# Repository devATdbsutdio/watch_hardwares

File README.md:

# watch_hardwares
PCB files and 3D files from each products and tools designed for the watch project, as exported from fusion360

License: [Apache License](https://github.com/devATdbsutdio/watch_hardwares/blob/main/LICENSE)

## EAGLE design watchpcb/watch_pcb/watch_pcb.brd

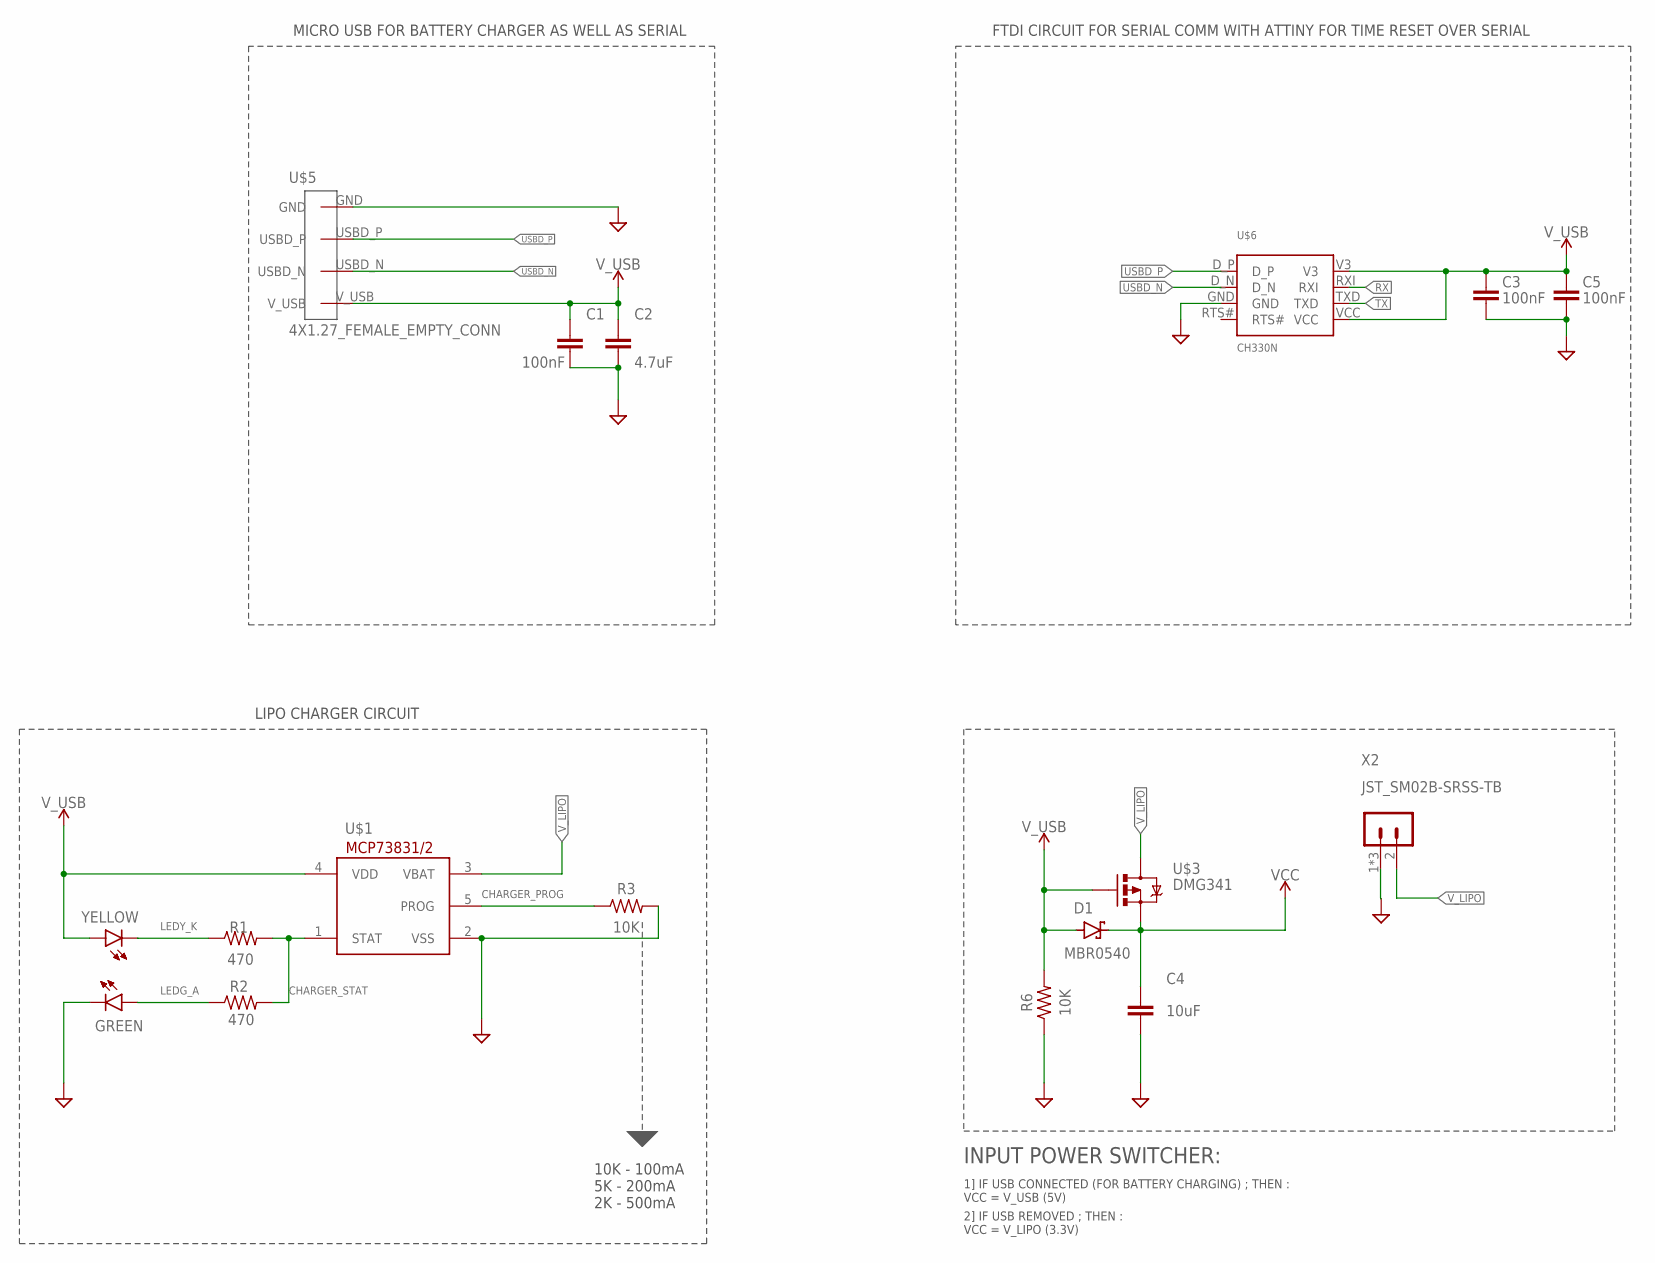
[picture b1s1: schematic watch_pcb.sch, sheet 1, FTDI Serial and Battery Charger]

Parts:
C1, C3, C5: 100nF; CAPC1005X60
C2: 4.7uF; CAPC1005X60
C4: 10uF; CAPC1005X60
D1: MBR0540; SOD-123
GREEN: GREEN; 2MMLED_GREEN
R1, R2: 470; RESC1005X40
R3, R6: 10K; RESC1005X40
U$1: MCP73831/2_LIPO_CHARGER; MCP73831_SOT23-5L
U$3: DMG341; DMG341-P_CHANNEL_MOSFET-SOT23
U$5: 4X1.27_FEMALE_EMPTY_CONN; 4X1.27_FEMALE_EMPTY_CONN-BACKUP
U$6: CH330N
X2: JST_SM02B-SRSS-TB; JST-SM02B-SRSS-TB
YELLOW: ORANGE; 2MMLED_YELLOW

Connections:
CHARGER_PROG: R3.1, U$1.5 (PROG)
CHARGER_STAT: R1.2, R2.2, U$1.1 (STAT)
GND: C1.2, C2.2, C3.2, C4.2, C5.2, GREEN.K (C), R3.2, R6.1, U$1.2 (VSS), U$5.GND, U$6.GND, X2.1, X2.M1 (1), X2.M2 (1); also elsewhere on the board
LEDG_A: GREEN.A, R2.1
LEDY_K: R1.1, YELLOW.K (C)
RX: U$6.RXI; also elsewhere on the board
TX: U$6.TXD; also elsewhere on the board
USBD_N: U$5.USBD_N, U$6.D_N
USBD_P: U$5.USBD_P, U$6.D_P
VCC: C4.1, D1.C, U$3.2 (S); also elsewhere on the board
V_LIPO: U$1.3 (VBAT), U$3.3 (D), X2.2; also elsewhere on the board
V_USB: C1.1, C2.1, C3.1, C5.1, D1.A, R6.2, U$1.4 (VDD), U$3.1 (G), U$5.V_USB, U$6.V3, U$6.VCC, YELLOW.A; also elsewhere on the board

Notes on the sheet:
10K - 100mA 5K - 200mA 2K - 500mA
FTDI CIRCUIT FOR SERIAL COMM WITH ATTINY FOR TIME RESET OVER SERIAL
MICRO USB FOR BATTERY CHARGER AS WELL AS SERIAL
LIPO CHARGER CIRCUIT
INPUT POWER SWITCHER:
1] IF USB CONNECTED (FOR BATTERY CHARGING) ; THEN : VCC = V_USB (5V)
2] IF USB REMOVED ; THEN : VCC = V_LIPO (3.3V)

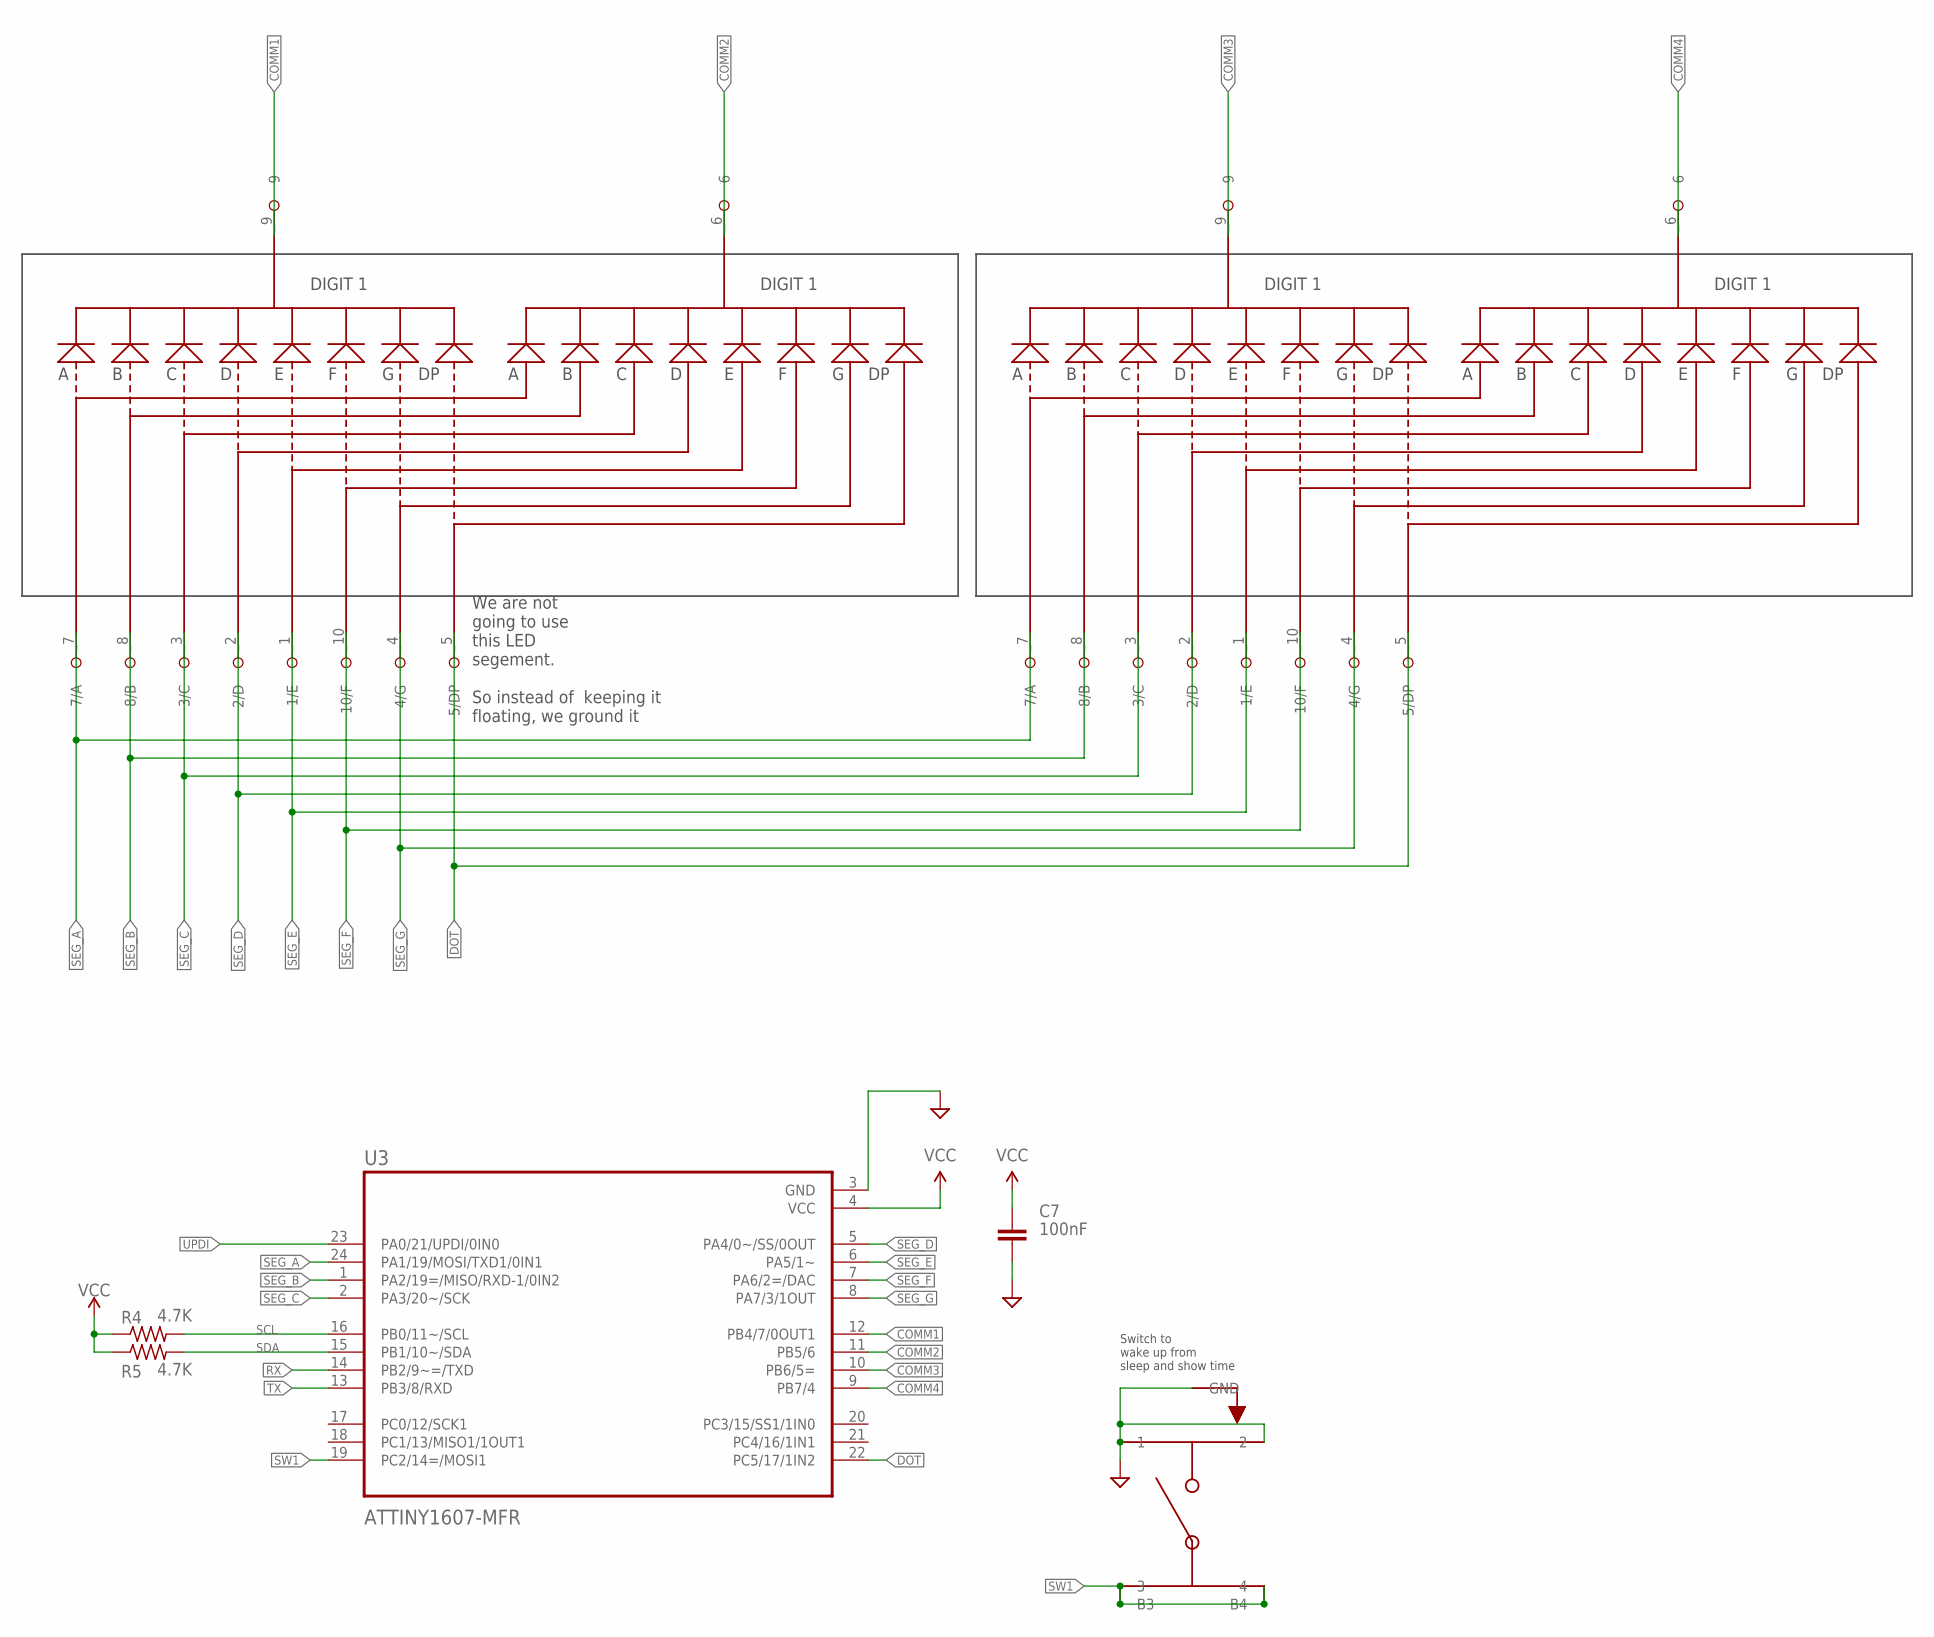
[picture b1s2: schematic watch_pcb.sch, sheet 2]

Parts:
BOT: 0.28-2DIGIT-7SEGEMNT; 2_DIGIT_0.28
C7: 100nF; CAPC1005X60
R4, R5: 4.7K; ADAFRUIT_R0402
TOP: 0.28-2DIGIT-7SEGEMNT; 2_DIGIT_0.28
U3: ATTINY1607-MFR; QFN50P400X400X90-25N
U$4: PTS840ESDPMSMTRLF

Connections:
COMM1: TOP._9 (9), U3.12 (PB4/7/0OUT1)
COMM2: TOP._6 (6), U3.11 (PB5/6)
COMM3: BOT._9 (9), U3.10 (PB6/5=)
COMM4: BOT._6 (6), U3.9 (PB7/4)
DOT: BOT._5 (5/DP), TOP._5 (5/DP), U3.22 (PC5/17/1IN2)
GND: C7.2, U3.3 (GND), U$4.1, U$4.2, U$4.5 (GND); also elsewhere on the board
RX: U3.14 (PB2/9~=/TXD); also elsewhere on the board
SCL: R4.2, U3.16 (PB0/11~/SCL); also elsewhere on the board
SDA: R5.2, U3.15 (PB1/10~/SDA); also elsewhere on the board
SEG_A: BOT._7 (7/A), TOP._7 (7/A), U3.24 (PA1/19/MOSI/TXD1/0IN1)
SEG_B: BOT._8 (8/B), TOP._8 (8/B), U3.1 (PA2/19=/MISO/RXD-1/0IN2)
SEG_C: BOT._3 (3/C), TOP._3 (3/C), U3.2 (PA3/20~/SCK)
SEG_D: BOT._2 (2/D), TOP._2 (2/D), U3.5 (PA4/0~/SS/0OUT)
SEG_E: BOT._1 (1/E), TOP._1 (1/E), U3.6 (PA5/1~)
SEG_F: BOT._10 (10/F), TOP._10 (10/F), U3.7 (PA6/2=/DAC)
SEG_G: BOT._4 (4/G), TOP._4 (4/G), U3.8 (PA7/3/1OUT)
SW1: U3.19 (PC2/14=/MOSI1), U$4.3, U$4.4, U$4.B3, U$4.B4
TX: U3.13 (PB3/8/RXD); also elsewhere on the board
UPDI: U3.23 (PA0/21/UPDI/0IN0); also elsewhere on the board
VCC: C7.1, R4.1, R5.1, U3.4 (VCC); also elsewhere on the board

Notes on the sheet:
Switch to wake up from sleep and show time
We are not going to use this LED segement. So instead of keeping it floating, we ground it

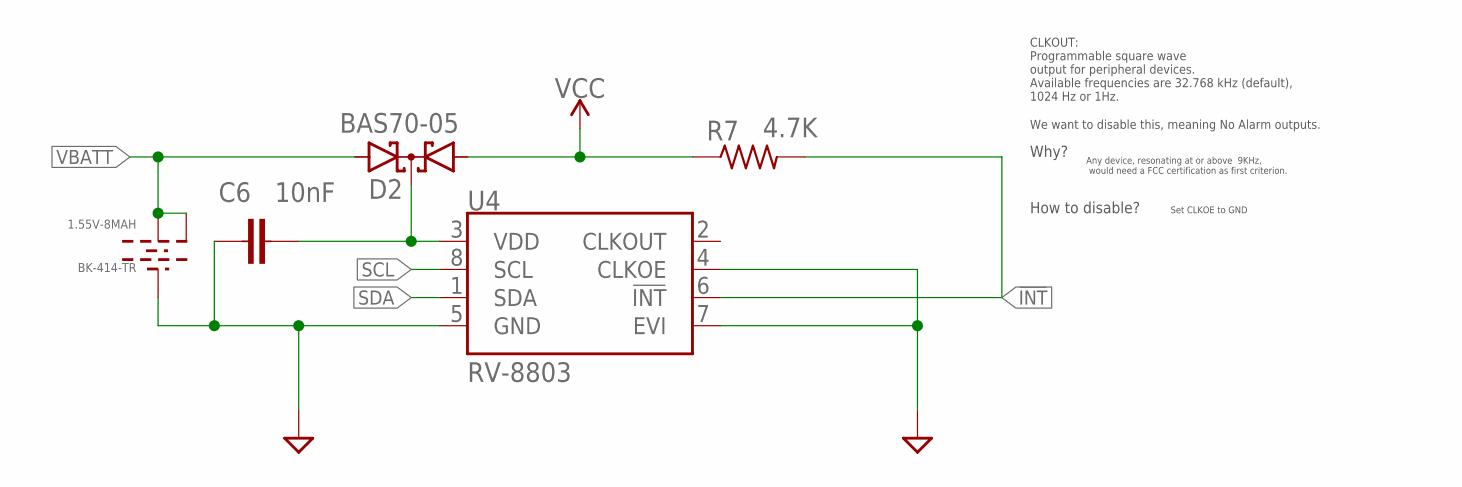
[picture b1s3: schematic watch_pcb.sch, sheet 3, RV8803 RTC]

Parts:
1.55V-8MAH: BK-414-TR
C6: 10nF; 0402-TIGHT
D2: BAS70-05; SOT23
R7: 4.7K; ADAFRUIT_R0402
U4: RV-8803; RV-3028

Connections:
!INT: R7.2, U4.6 (!INT)
GND: 1.55V-8MAH.- (_GND), C6.2, U4.4 (CLKOE), U4.5 (GND), U4.7 (EVI); also elsewhere on the board
SCL: U4.8 (SCL); also elsewhere on the board
SDA: U4.1 (SDA); also elsewhere on the board
VBATT: 1.55V-8MAH.1+ (VOUT), 1.55V-8MAH.2+ (VOUT2), D2.2 (A2)
VCC: D2.1 (A1), R7.1; also elsewhere on the board
VDD1: C6.1, D2.3 (C), U4.3 (VDD)

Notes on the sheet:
CLKOUT: Programmable square wave output for peripheral devices. Available frequencies are 32.768 kHz (default), 1024 Hz or 1Hz.
We want to disable this, meaning No Alarm outputs.
Why?
How to disable?
Set CLKOE to GND
Any device, resonating at or above 9KHz, would need a FCC certification as first criterion.

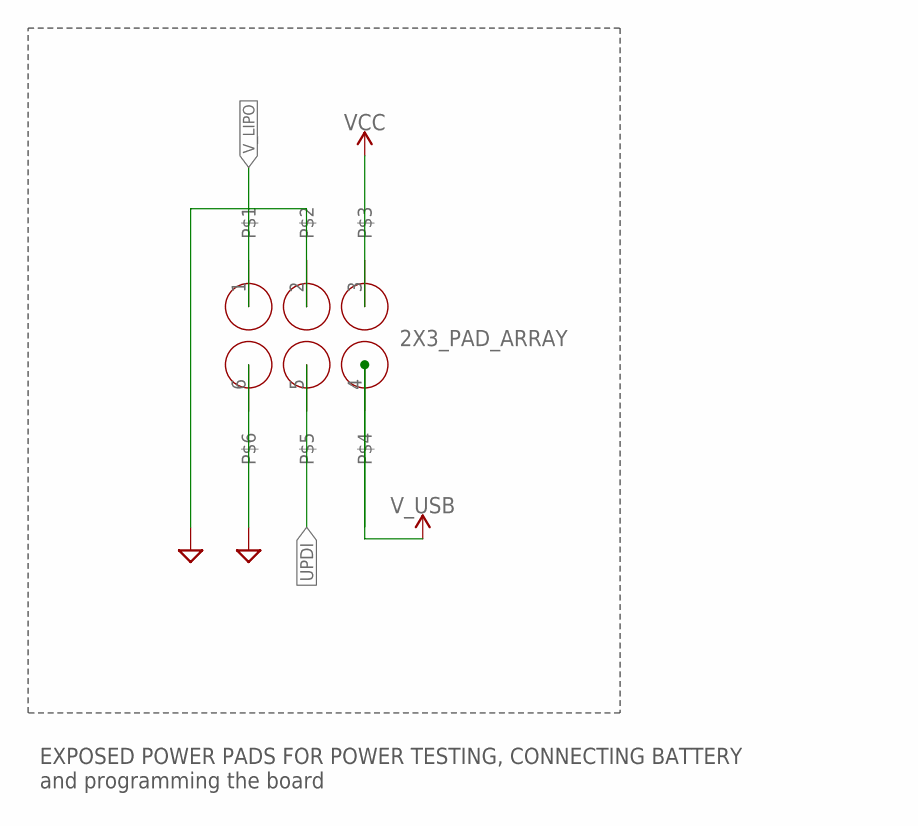
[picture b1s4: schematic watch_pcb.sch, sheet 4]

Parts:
U$2: 2X3_PAD_ARRAY

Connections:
GND: U$2.2, U$2.6; also elsewhere on the board
UPDI: U$2.5; also elsewhere on the board
VCC: U$2.3; also elsewhere on the board
V_LIPO: U$2.1; also elsewhere on the board
V_USB: U$2.4; also elsewhere on the board

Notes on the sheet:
EXPOSED POWER PADS FOR POWER TESTING, CONNECTING BATTERY and programming the board

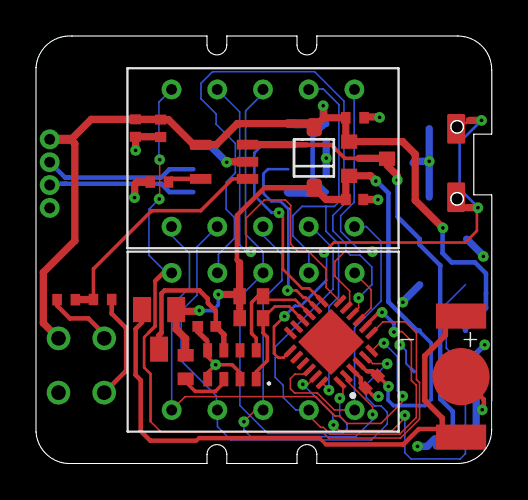
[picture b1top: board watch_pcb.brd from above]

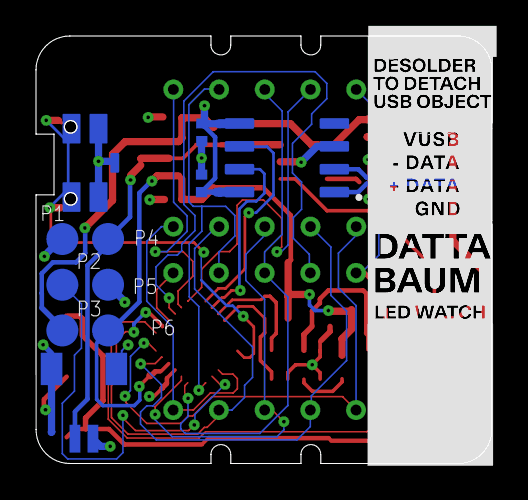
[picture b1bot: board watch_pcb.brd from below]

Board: 4 copper layers, 25.3 x 23.7 mm, 30 parts (6 on the bottom side), 31 nets.

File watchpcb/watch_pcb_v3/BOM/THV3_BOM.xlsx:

Total boards | 250
Value | Device | Package | Parts | Description | Qty | Unit Price | Total Price | Notes1 | Notes2 | Notes 3
100nF | C_CHIP-0402(1005-METRIC) | C-0402 SMT | C1, C3, C5, C7 | Capacitor - Generic | 4 |  | 0
10nF | C_CHIP-0402(1005-METRIC) | C-0402 SMT | C6 | Capacitor - Generic | 1 |  | 0
10uF | C_CHIP-0402(1005-METRIC) | C-0402 SMT | C4 | Capacitor - Generic | 1 |  | 0
4.7uF | C_CHIP-0402(1005-METRIC) | C-0402 SMT | C2 | Capacitor - Generic | 1 |  | 0
470 | R-US_CHIP-0402(1005-METRIC) | R0402 SMT | R1, R2 | Resistor Fixed - ANSI | 2 |  | 0
10K | R-US_CHIP-0402(1005-METRIC) | R0402 SMT | R3, R6 | Resistor Fixed - ANSI | 2 |  | 0
4.7K | R-US_CHIP-0402(1005-METRIC) | R0402 SMT | R4, R5, R7 | RESISTOR, American symbol | 3 |  | 0
BAS70-05 | BAS70-05 | SOT23 | D2 | Silicon Schottky Diodes | 1 |  | 0
MBR0540 | MBR0520LT1G | SOD-123 | D1 | DIODE SCHOTTKY SOD123 | 1 |  | 0
DMG341 | P_CHANNEL_MOSFET-SOT23 | P_CHANNEL_MOSFET-SOT23 | U$3 | MOSFET | 1 |  | 0
MCP73831/2 | MCP73831/2_LIPO_CHARGER | MCP73831_SOT23-5L | U$1 | LiPo Charger | 1 |  | 0
RV-8803 | RV-8803 | RV-3028 | U4 | Micro Crystal RV-8803 RTC | 1 |  | 0
ATTINY1607-MFR | ATTINY1607-MNR | QFN50P400X400X90-25N | U3 | None Check prices | 1 |  | 0
CH330N | CH330N | SOT8 | U$6 | USB to Serial Chip | 1 |  | 0
PTS840ESDPMSMTRLF | PTS840ESDPMSMTRLF | PTS840ESDPMSMTRLF | U$4 | Push Button | 1 |  | 0 | https://item.taobao.com/item.htm?spm=a1z09.2.0.0.605f2e8dPbD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
JST_SM02B-SRSS-TB | JST_SM02B-SRSS-TB | JST-SM02B-SRSS-TB | X2 | LiPo Battery Connector | 1 |  | 0 | I have, But it is not in tape but in a pipe. I can send you then you don’t have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
BK-414-TR | BK-414-TR | NaN | 1.55V-8MAH | Coin cell holder for micro coin cell for the RTC. | 1 | 5 | 1250 | I have the Tape reel of the connectors. I can send you. No need to buy. But buy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 | Need to purchase the coin cells. Coin cell: SR416SW Panansonic China Seller: ht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
0.28-2DIGIT-7SEGEM | 0.28-2DIGIT-7SEGEMNT | 2_DIGIT_0.28 | BOT, TOP | 0.2" Common Anode 7 segment display with white LEDs | 2 | 1.1499999999999999 | 575 | 2 digit, Common Cathode, White LED | China Seller: https://item.taobao.com/item.htm?spm=a1z09.2.0.0.605f2e8dPbDM7b&i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 | 1. Procure the part. 2. Cut the leads to length: 3. Send to me. 4. I will send 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 | This is the orientation it needs to be mounted on the board at last

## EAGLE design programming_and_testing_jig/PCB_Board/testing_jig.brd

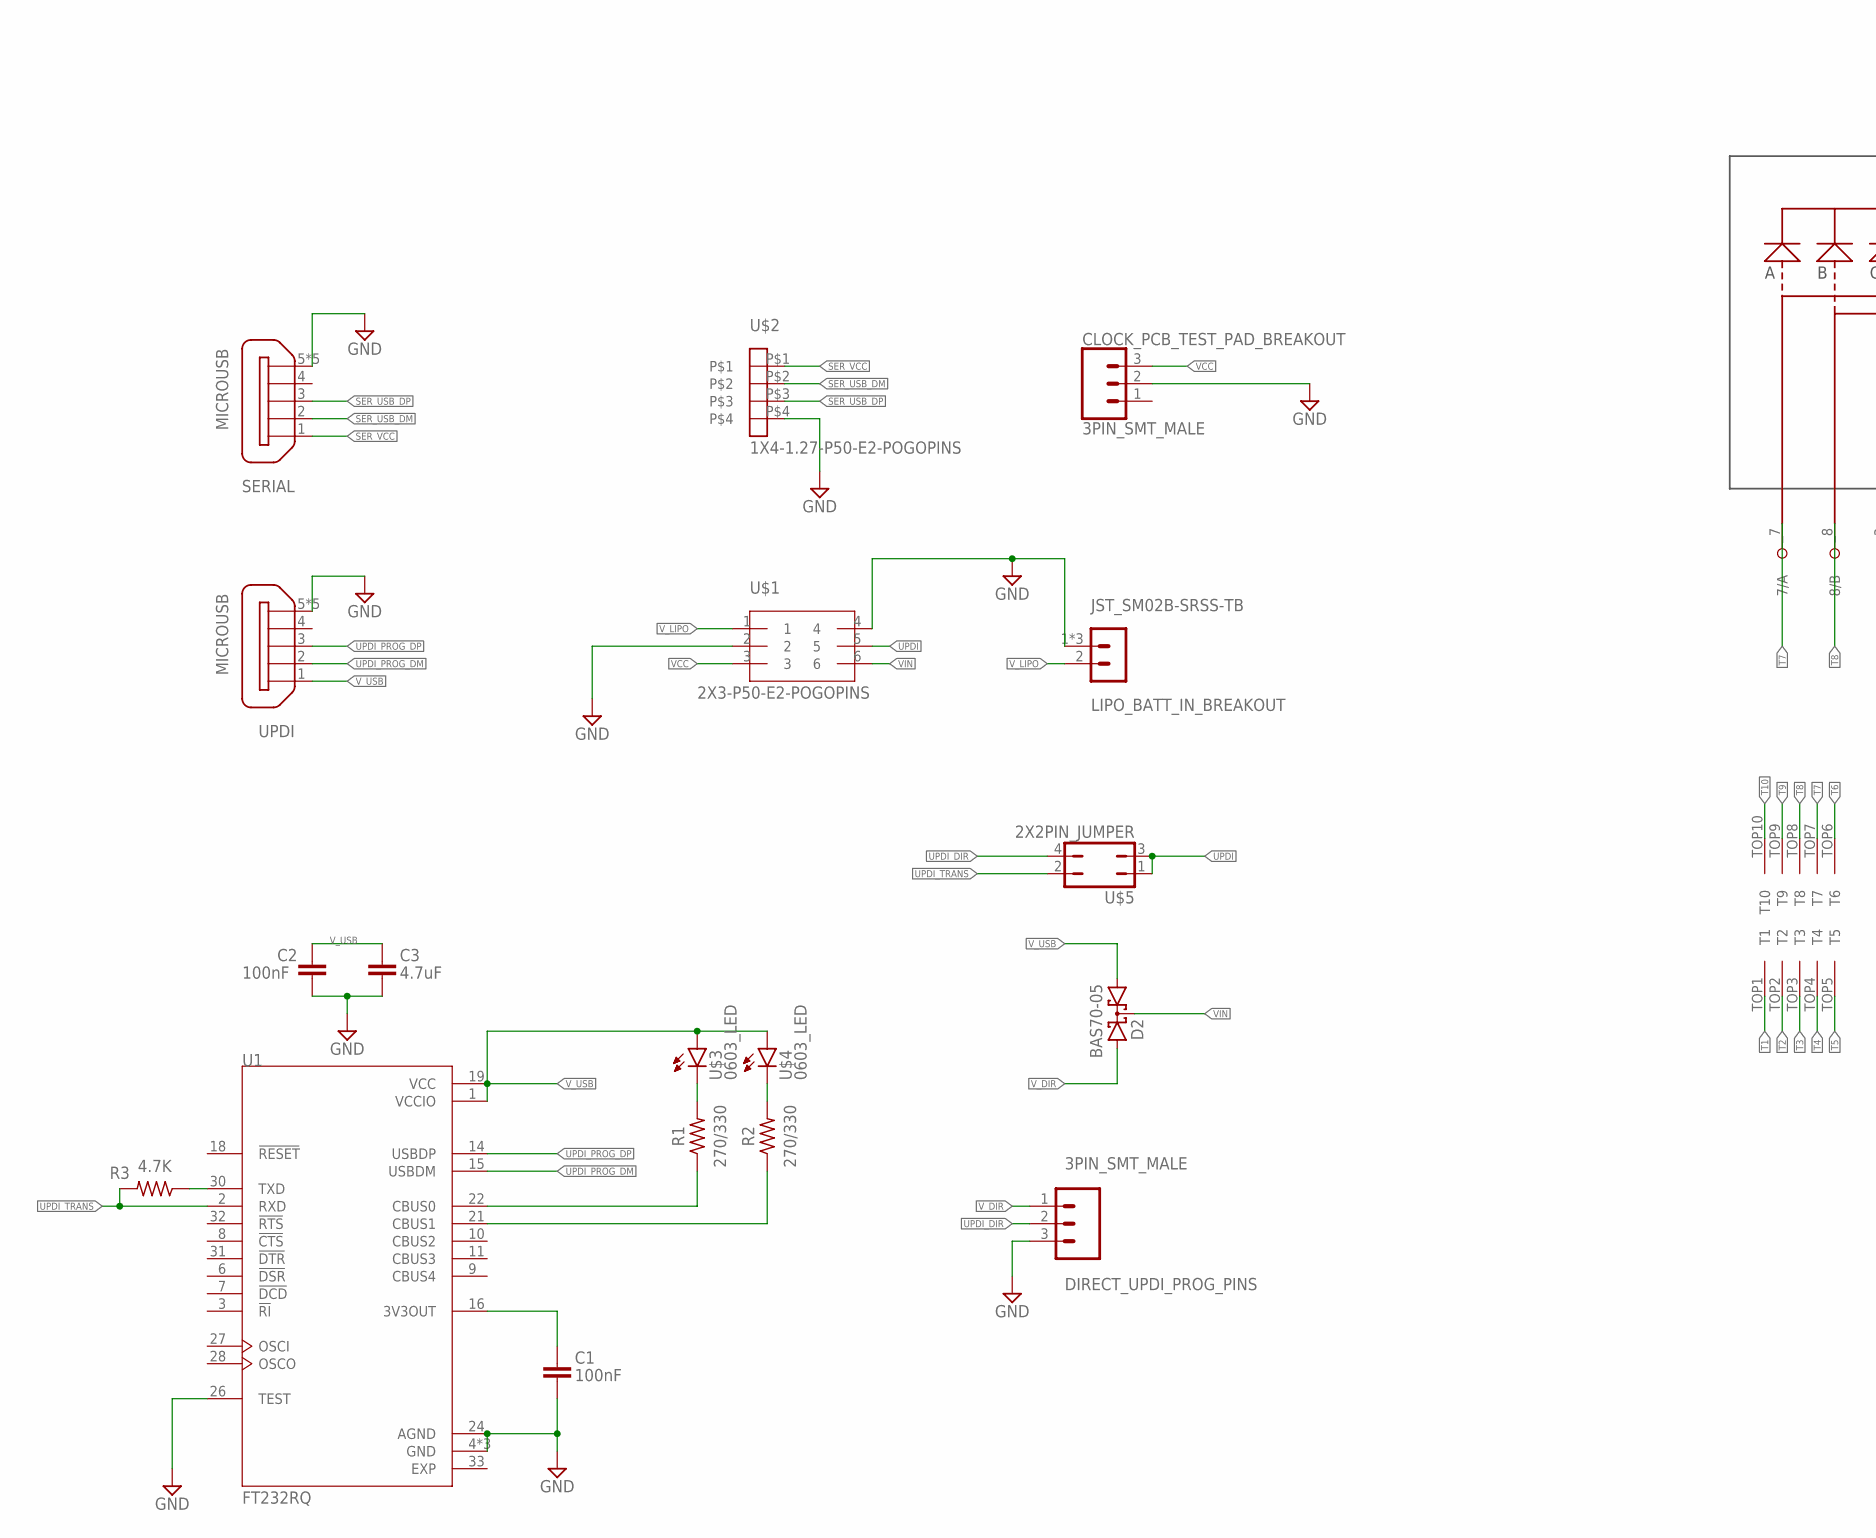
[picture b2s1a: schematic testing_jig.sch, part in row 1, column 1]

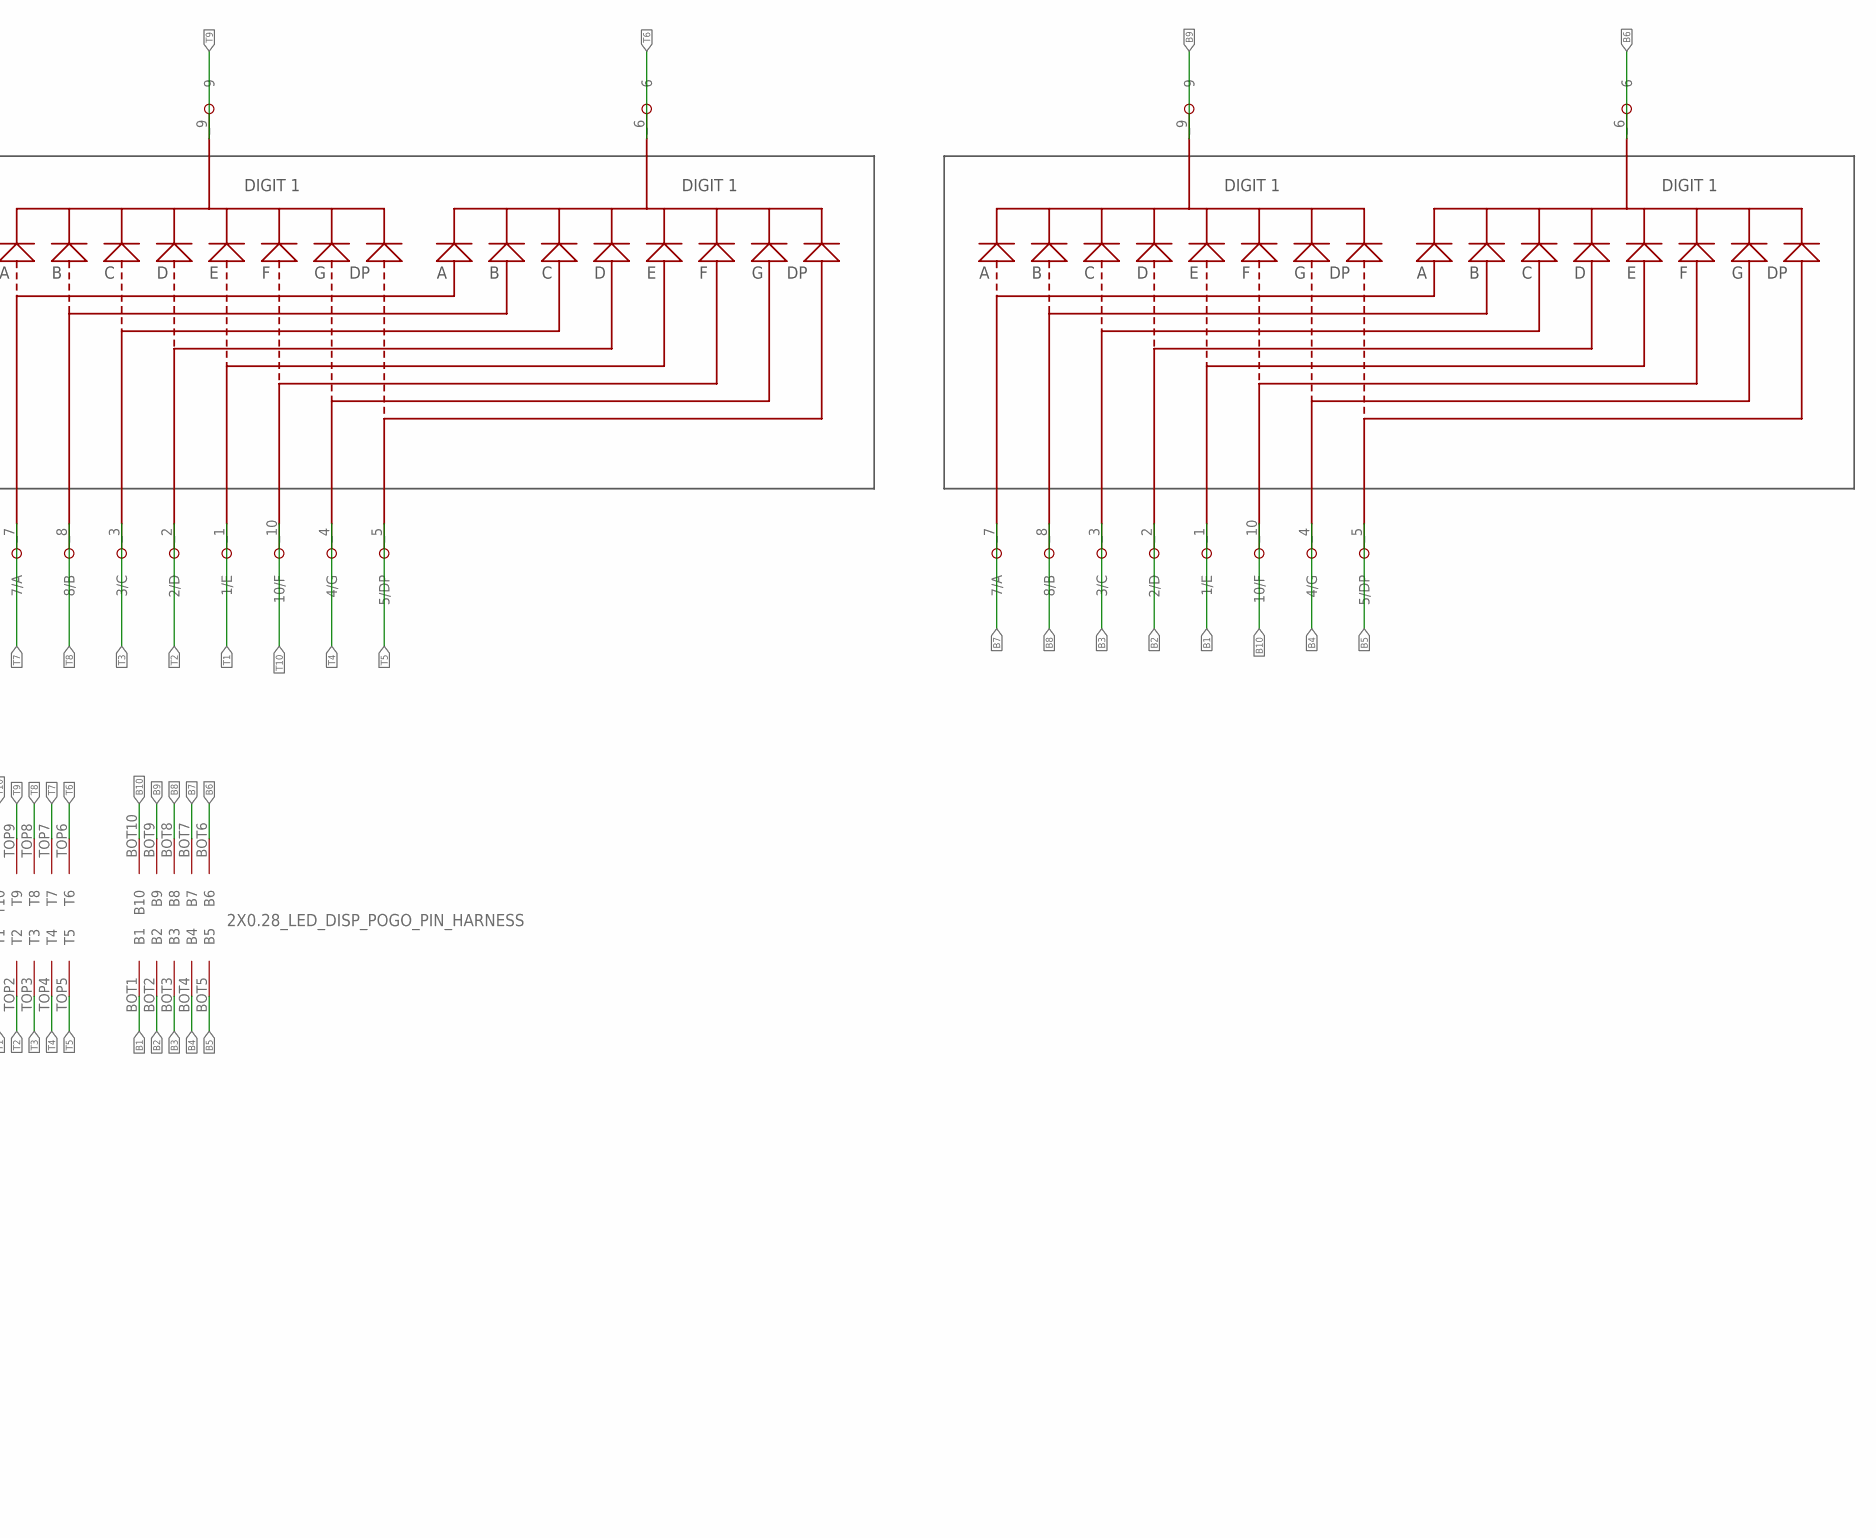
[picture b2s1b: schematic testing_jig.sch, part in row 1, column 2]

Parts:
BOTTOM: 0.28"-2DIGIT-7SEGEMNT; 2_DIGIT_0.28"
C1, C2: 100nF; 0603CAP
C3: 4.7uF; 0603CAP
CLOCK_PCB_TEST_PAD_BREAKOUT: 3PIN_SMT_MALE; 3PIN__SMT_MALE
D2: BAS70-05; SOT23
DIRECT_UPDI_PROG_PINS: 3PIN_SMT_MALE; 3PIN__SMT_MALE
LIPO_BATT_IN_BREAKOUT: JST_SM02B-SRSS-TB; JST-SM02B-SRSS-TB
R1, R2: 270/330; RESC1608X60
R3: 4.7K; RESC1608X60
SERIAL: MICROUSB; ZX62D-B-5PA8
TOP: 0.28"-2DIGIT-7SEGEMNT; 2_DIGIT_0.28"
U1: FT232RQ; QFN50P500X500X90-33N
U$1: 2X3-P50-E2-POGOPINS
U$2: 1X4-1.27-P50-E2-POGOPINS
U$3, U$4: 0603_LED
U$5: 2X2PIN_JUMPER
U$6: 2X0.28_LED_DISP_POGO_PIN_HARNESS
UPDI: MICROUSB; ZX62D-B-5PA8

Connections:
3V3OUT: C1.1, U1.16 (3V3OUT)
B1: BOTTOM._1 (1/E), U$6.BOT1 (B1)
B2: BOTTOM._2 (2/D), U$6.BOT2 (B2)
B3: BOTTOM._3 (3/C), U$6.BOT3 (B3)
B4: BOTTOM._4 (4/G), U$6.BOT4 (B4)
B5: BOTTOM._5 (5/DP), U$6.BOT5 (B5)
B6: BOTTOM._6 (6), U$6.BOT6 (B6)
B7: BOTTOM._7 (7/A), U$6.BOT7 (B7)
B8: BOTTOM._8 (8/B), U$6.BOT8 (B8)
B9: BOTTOM._9 (9), U$6.BOT9 (B9)
B10: BOTTOM._10 (10/F), U$6.BOT10 (B10)
CBUS0: R1.1, U1.22 (CBUS0)
CBUS1: R2.1, U1.21 (CBUS1)
EXP: U1.33 (EXP)
GND: C1.2, C2.2, C3.2, CLOCK_PCB_TEST_PAD_BREAKOUT.2, DIRECT_UPDI_PROG_PINS.3, LIPO_BATT_IN_BREAKOUT.1, LIPO_BATT_IN_BREAKOUT.M1 (1), LIPO_BATT_IN_BREAKOUT.M2 (1), SERIAL.5, SERIAL.S1 (5), SERIAL.S2 (5), SERIAL.S3 (5), SERIAL.S4 (5), U1.4 (GND), U1.17 (GND), U1.20 (GND), U1.24 (AGND), U1.26 (TEST), U$1.2, U$1.4, U$2.P$4, UPDI.5, UPDI.S1 (5), UPDI.S2 (5), UPDI.S3 (5), UPDI.S4 (5)
unnamed: R1.2, U$3.C
unnamed: R2.2, U$4.C
SER_USB_DM: SERIAL.2, U$2.P$2
SER_USB_DP: SERIAL.3, U$2.P$3
SER_VCC: SERIAL.1, U$2.P$1
T1: TOP._1 (1/E), U$6.TOP1 (T1)
T2: TOP._2 (2/D), U$6.TOP2 (T2)
T3: TOP._3 (3/C), U$6.TOP3 (T3)
T4: TOP._4 (4/G), U$6.TOP4 (T4)
T5: TOP._5 (5/DP), U$6.TOP5 (T5)
T6: TOP._6 (6), U$6.TOP6 (T6)
T7: TOP._7 (7/A), U$6.TOP7 (T7)
T8: TOP._8 (8/B), U$6.TOP8 (T8)
T9: TOP._9 (9), U$6.TOP9 (T9)
T10: TOP._10 (10/F), U$6.TOP10 (T10)
TXD: R3.1, U1.30 (TXD)
UPDI: U$1.5, U$5.1, U$5.3
UPDI_DIR: DIRECT_UPDI_PROG_PINS.2, U$5.4
UPDI_PROG_DM: U1.15 (USBDM), UPDI.2
UPDI_PROG_DP: U1.14 (USBDP), UPDI.3
UPDI_TRANS: R3.2, U1.2 (RXD), U$5.2
VCC: CLOCK_PCB_TEST_PAD_BREAKOUT.3, U$1.3
VIN: D2.3 (C), U$1.6
V_DIR: D2.2 (A2), DIRECT_UPDI_PROG_PINS.1
V_LIPO: LIPO_BATT_IN_BREAKOUT.2, U$1.1
V_USB: C2.1, C3.1, D2.1 (A1), U1.1 (VCCIO), U1.19 (VCC), U$3.A, U$4.A, UPDI.1

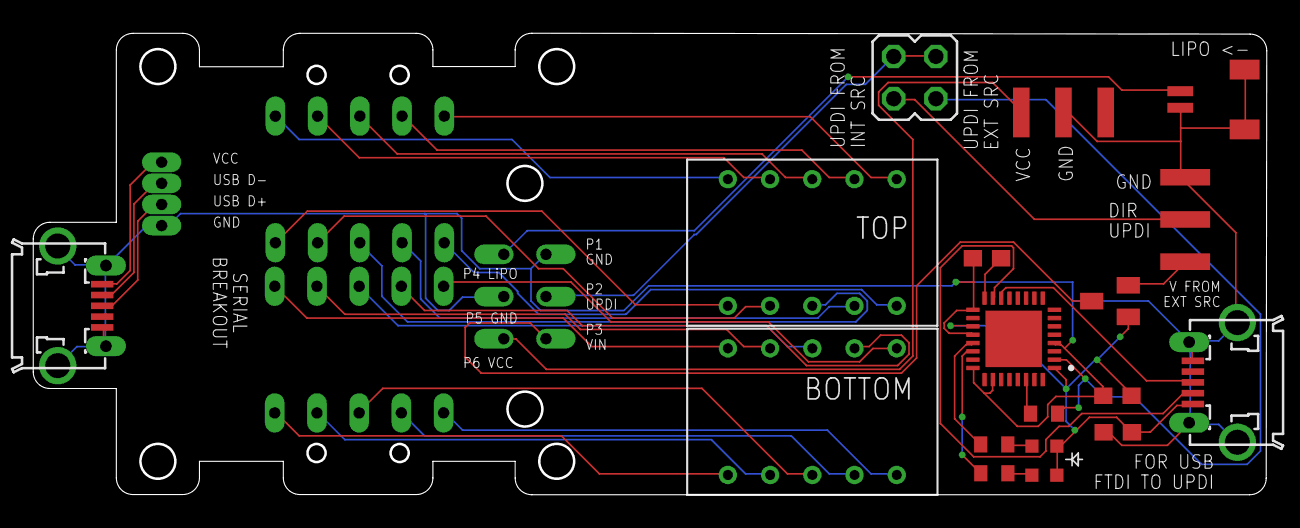
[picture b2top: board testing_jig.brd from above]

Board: 2 copper layers, 74.1 x 27.6 mm, 21 parts (0 on the bottom side), 40 nets.

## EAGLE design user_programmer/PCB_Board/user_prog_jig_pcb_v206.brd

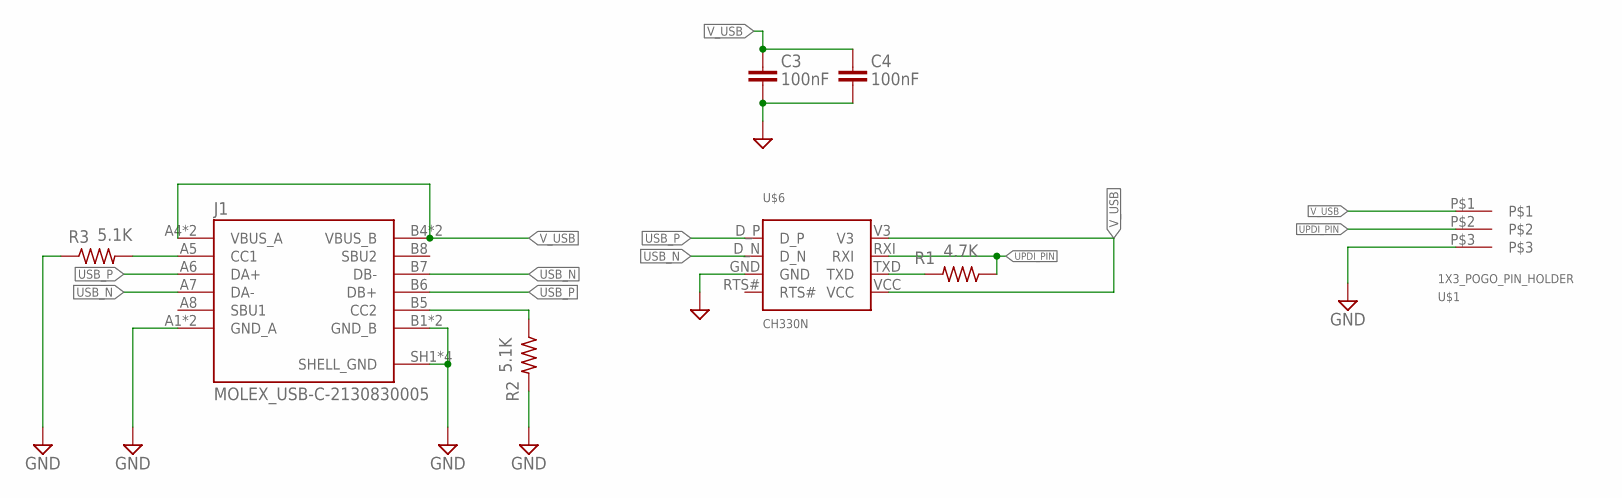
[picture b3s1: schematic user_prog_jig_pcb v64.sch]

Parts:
C3, C4: 100nF; CAPC1005X60
J1: MOLEX_USB-C-2130830005; MOLEX_2130830005
R1: 4.7K; RESC1005X40
R2, R3: 5.1K; RESC1005X40
U$1: 1X3_POGO_PIN_HOLDER
U$6: CH330N

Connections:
CC1: J1.A5 (CC1), R3.2
CC2: J1.B5 (CC2), R2.1
GND: C3.2, C4.2, J1.A1 (GND_A), J1.A12 (GND_A), J1.B1 (GND_B), J1.B12 (GND_B), J1.SH1 (SHELL_GND), J1.SH2 (SHELL_GND), J1.SH3 (SHELL_GND), J1.SH4 (SHELL_GND), R2.2, R3.1, U$1.P$3, U$6.GND
unnamed: R1.2, U$6.TXD
UPDI_PIN: R1.1, U$1.P$2, U$6.RXI
USB_N: J1.A7 (DA-), J1.B7 (DB-), U$6.D_N
USB_P: J1.A6 (DA+), J1.B6 (DB+), U$6.D_P
V_USB: C3.1, C4.1, J1.A4 (VBUS_A), J1.A9 (VBUS_A), J1.B4 (VBUS_B), J1.B9 (VBUS_B), U$1.P$1, U$6.V3, U$6.VCC

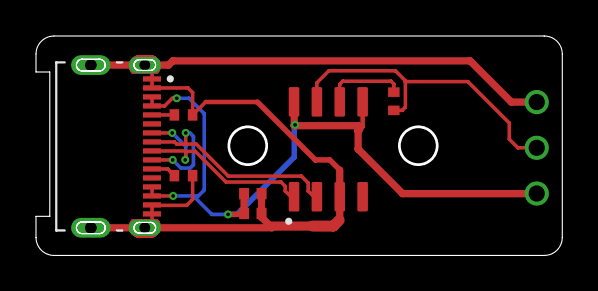
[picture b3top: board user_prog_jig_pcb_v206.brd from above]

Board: 2 copper layers, 29.1 x 12.0 mm, 8 parts (1 on the bottom side), 8 nets.

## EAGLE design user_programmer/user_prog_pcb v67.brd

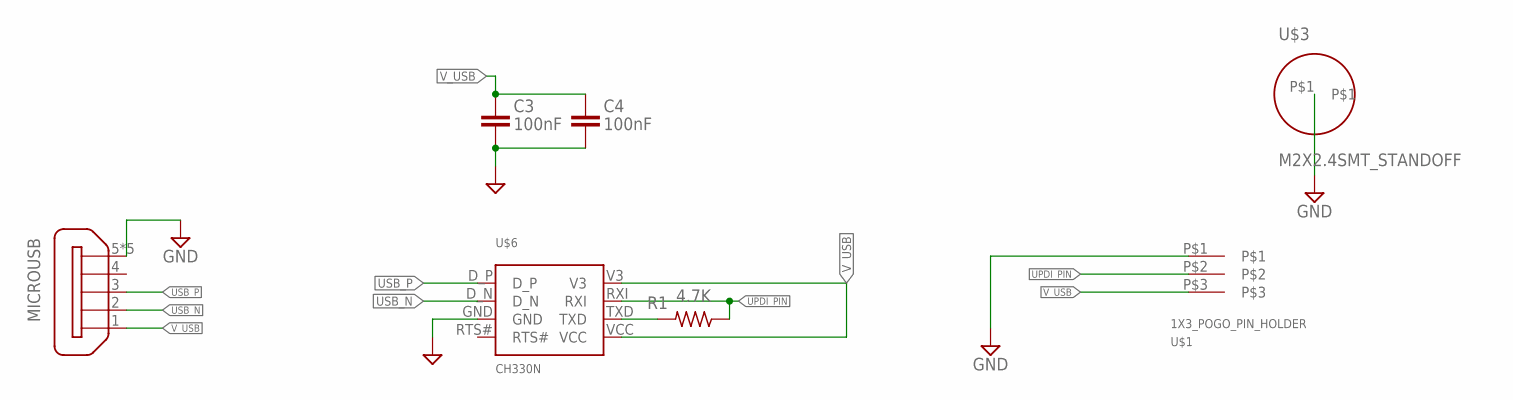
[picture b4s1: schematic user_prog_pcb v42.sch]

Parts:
C3, C4: 100nF; CAPC1005X60
R1: 4.7K; RESC1005X40
U$1: 1X3_POGO_PIN_HOLDER
U$3: M2X2.4SMT_STANDOFF
U$6: CH330N
UPDI: MICROUSB; ZX62D-B-5PA8

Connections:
GND: C3.2, C4.2, U$1.P$1, U$3.P$1, U$6.GND, UPDI.5, UPDI.S1 (5), UPDI.S2 (5), UPDI.S3 (5), UPDI.S4 (5)
unnamed: R1.2, U$6.TXD
UPDI_PIN: R1.1, U$1.P$2, U$6.RXI
USB_N: U$6.D_N, UPDI.2
USB_P: U$6.D_P, UPDI.3
V_USB: C3.1, C4.1, U$1.P$3, U$6.V3, U$6.VCC, UPDI.1

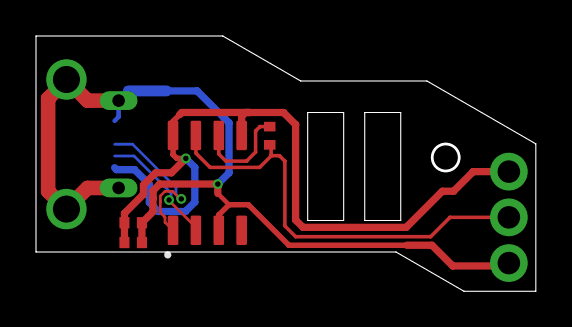
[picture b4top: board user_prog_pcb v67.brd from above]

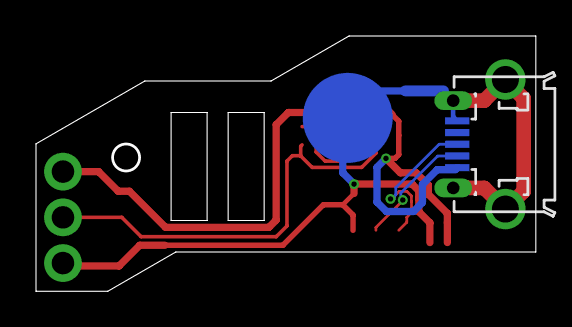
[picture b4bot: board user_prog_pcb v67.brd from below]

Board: 2 copper layers, 27.6 x 14.0 mm, 7 parts (2 on the bottom side), 6 nets.

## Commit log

2022-04-21 added watch pcb gerber files
2022-04-21 Create LICENSE
2022-04-21 added exported pcb files from f3d for user prog jig
2022-04-22 some folder arrangements and added GERBER exports
2022-04-22 added some pictures
2022-05-25 long time no see
2022-05-26 watch pcb verison name change in folder
2022-05-26 added stackup info
2022-05-26 added BOM for watch
2022-05-26 added PnP an folder restructre in watchpcb DIR
2022-05-26 added component testing jig DIR
2022-06-01 new jig modification exports
2022-06-04 new user programmer micro usb replacement
2022-06-10 micro usb version slim shell added

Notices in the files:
parts and their libraries:
SparkFun-Capacitors: Licensing: Creative Commons ShareAlike 4.0 International - https://creativecommons.org/licenses/by-sa/4.0
